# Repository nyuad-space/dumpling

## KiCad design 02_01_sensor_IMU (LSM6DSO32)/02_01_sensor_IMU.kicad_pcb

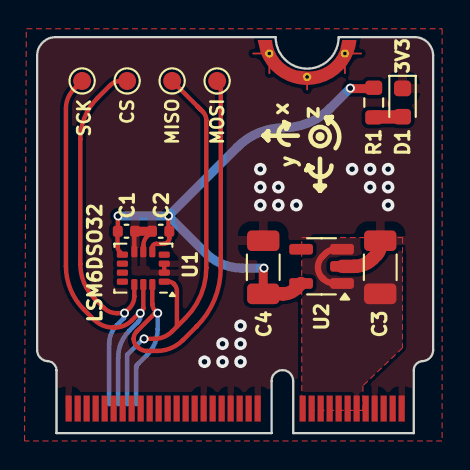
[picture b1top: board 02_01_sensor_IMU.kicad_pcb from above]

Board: 2 copper layers, 22.0 x 22.0 mm, 15 parts (0 on the bottom side), 10 nets.

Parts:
C1, C2: 100n; C_0402_1005Metric
C3, C4: 10u; C_1206_3216Metric
CS: SPI3; TestPoint_Pad_D1.0mm
D1: LED; LED_0603_1608Metric
FRAME1: FRAME-LEDGER; CREATIVE_COMMONS
J1: MICROMOD-2222; M.2-CARD-E-22
LOGO1: SPECIAL_INSTRUCTIONS-ORDERING; ORDERING_INSTRUCTIONS
MISO: SPI3; TestPoint_Pad_D1.0mm
MOSI: SPI3; TestPoint_Pad_D1.0mm
R1: 10k; R_0603_1608Metric
SCK: SPI3; TestPoint_Pad_D1.0mm
U1: LSM6DSO32TR; LGA-14_3x2.5mm_P0.5mm_LayoutBorder3x4y
U2: AP2112K-3.3; SOT-23-5

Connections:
+3V3: C1.1, C2.1, C4.1, J1.2 (3.3V), J1.74 (3.3V), R1.1, U1.5 (VDDIO), U1.8 (VDD), U2.5 (VOUT)
GND: C1.2, C2.2, C3.2, C4.2, D1.1 (K), J1.1 (GND), J1.7 (GND), J1.33 (GND), J1.36 (GND), J1.39 (GND), J1.45 (GND), J1.75 (GND), J1.GND1 (GND), J1.GND2 (GND), J1.GND3 (GND), U1.2 (SDx), U1.3 (SCx), U1.6 (GND), U1.7 (GND), U2.2 (GND)
LSM6DSO32TR_CS: CS.1, J1.66 (SDIO_DATA1), U1.12 (CS)
LSM6DSO32TR_INT1: J1.44 (G2/BUS2), U1.4 (INT1)
LSM6DSO32TR_INT2: J1.46 (G3/BUS3), U1.9 (INT2)
LSM6DSO32TR_MISO: J1.62 (SPI_SDO1/SDIO_CMD), MISO.1, U1.1 (SDO/SA0)
LSM6DSO32TR_MOSI: J1.60 (SPI_SCK1/SDIO_CLK), MOSI.1, U1.14 (SDA)
LSM6DSO32TR_SCK: J1.64 (SPI_SDI1/SDIO_DATA0), SCK.1, U1.13 (SCL)
unnamed: D1.2 (A), R1.2
VIN: C3.1, J1.11 (~BOOT), U2.1 (VIN), U2.3 (EN)

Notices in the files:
parts and their libraries:
Released under the Creative Commons Attribution Share-Alike 4.0 License
https://creativecommons.org/licenses/by-sa/4.0
